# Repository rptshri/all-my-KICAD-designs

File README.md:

View this project on [CADLAB.io](https://cadlab.io/project/2196). 

# all-my-KICAD-designs

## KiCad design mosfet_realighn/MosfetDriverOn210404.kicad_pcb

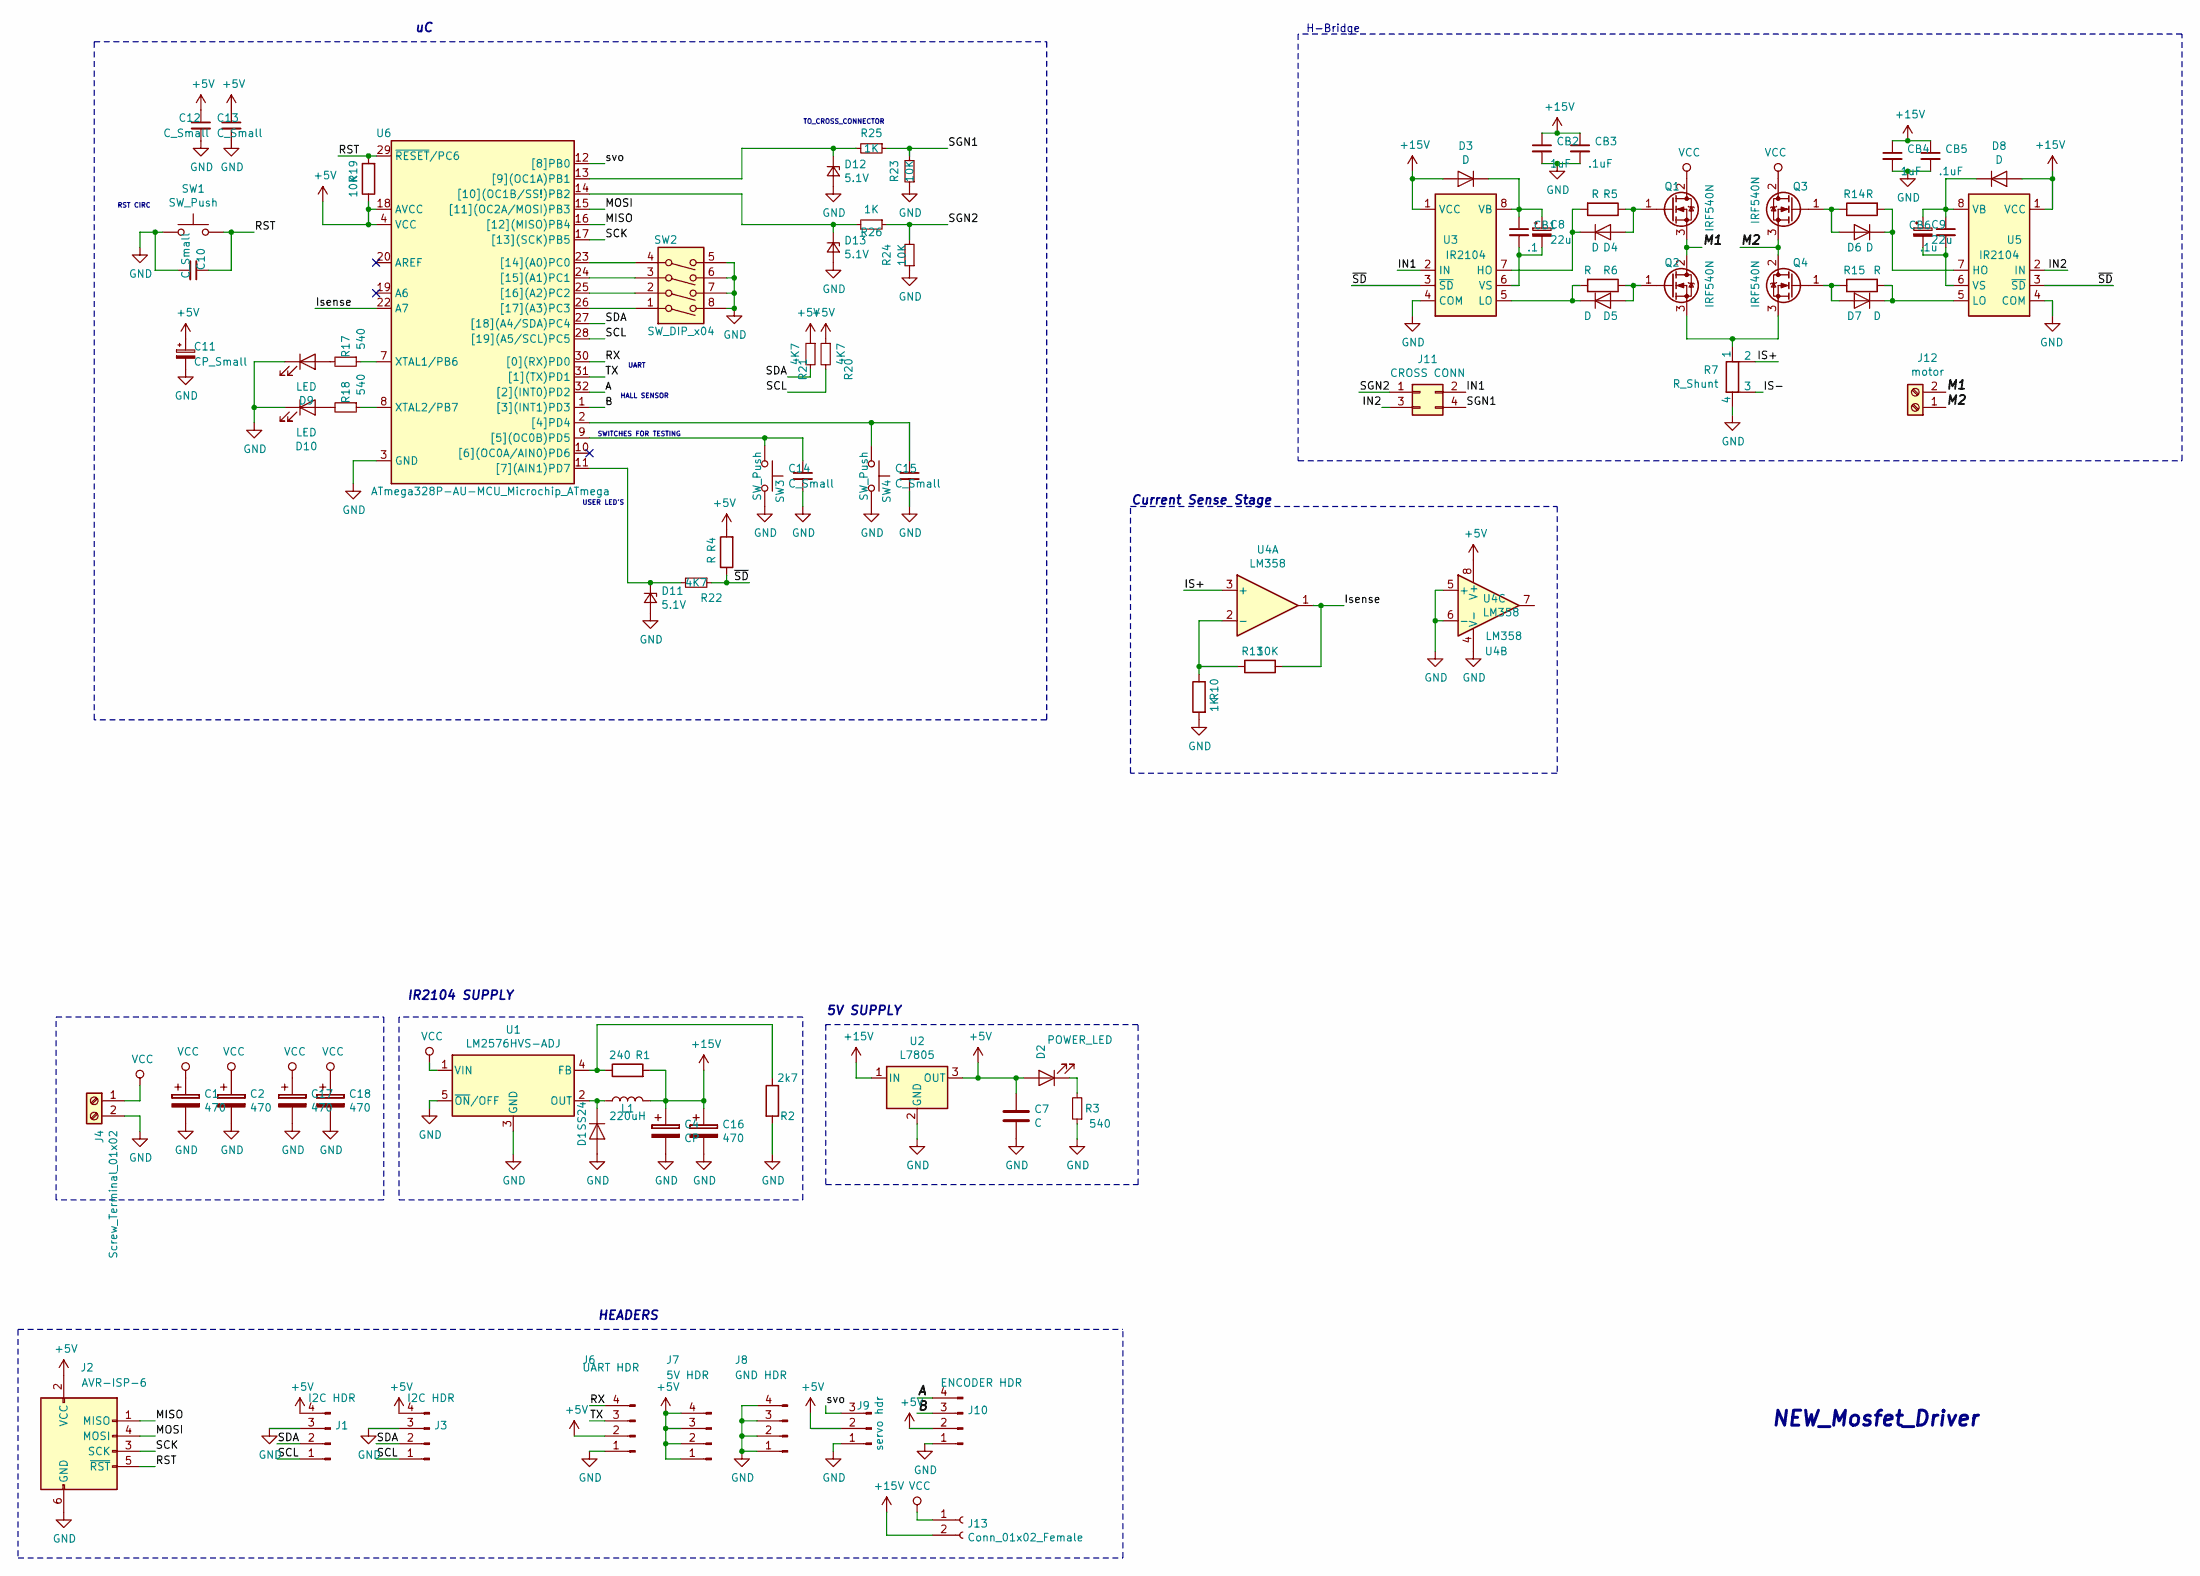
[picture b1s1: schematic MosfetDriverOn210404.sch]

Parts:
C1, C2: 470; CP_Elec_8x6.2
C4: CP; CP_Elec_6.3x5.7
C7: C; C_0603_1608Metric
C8, C9: 22u; CP_Elec_6.3x5.7
C10, C12, C13, C14, C15: C_Small; C_0603_1608Metric
C11: CP_Small; CP_Elec_5x4.4
C16: 470; CP_Elec_6.3x5.7
C17, C18: 470; CP_Elec_10x7.9
CB1: .1; C_0603_1608Metric
CB2, CB4: 1uF; C_0603_1608Metric
CB3, CB5: .1uF; C_0603_1608Metric
CB6: .1u; C_0603_1608Metric
D1: SS24; D_SMA
D2: POWER_LED; LED_0603_1608Metric
D3, D4, D5, D6, D7, D8: D; D_SMA
D9, D10: LED; LED_0603_1608Metric
D11, D12, D13: 5.1V; D_SMA
J1, J3: I2C HDR; JST_PH_B4B-PH-K_1x04_P2.00mm_Vertical
J2: AVR-ISP-6; PinHeader_2x03_P2.54mm_Vertical
J4: Screw_Terminal_01x02; PhoenixContact_MSTBA_2,5_2-G_1x02_P5.00mm_Horizontal
J6: UART HDR; PinHeader_1x04_P2.54mm_Vertical
J7: 5V HDR; PinHeader_1x04_P2.54mm_Vertical
J8: GND HDR; PinHeader_1x04_P2.54mm_Vertical
J9: servo hdr; PinSocket_1x03_P2.54mm_Vertical
J10: ENCODER HDR; PinHeader_1x04_P2.54mm_Vertical
J11: CROSS CONN; PinHeader_2x02_P2.54mm_Vertical
J12: motor; PhoenixContact_MSTBA_2,5_2-G_1x02_P5.00mm_Horizontal
J13: Conn_01x02_Female; PinHeader_1x02_P2.54mm_Vertical
L1: 220uH; L_12x12mm_H6mm
Q1: IRF540N; TO-220-3_Vertical
Q2, Q3, Q4: IRF540N; TO220_HS_SCREW
R1: 240; R_0603_1608Metric
R2: 2k7; R_0603_1608Metric
R3, R17, R18: 540; R_0603_1608Metric
R4, R5, R6, R14, R15: R; R_0603_1608Metric
R7: R_Shunt; Shunt_Resistor-2mohm
R10, R25, R26: 1K; R_0603_1608Metric
R13, R19, R23, R24: 10K; R_0603_1608Metric
R20, R21, R22: 4K7; R_0603_1608Metric
SW1, SW3, SW4: SW_Push; SW_SPST_CK_RS282G05A3
SW2: SW_DIP_x04; SW_DIP_SPSTx04_Slide_9.78x12.34mm_W7.62mm_P2.54mm
U1: LM2576HVS-ADJ; TO-263-5_TabPin3
U2: L7805; SOT-223-3_TabPin2
U3, U5: IR2104; DIP-8_W7.62mm_Socket_LongPads
U4: LM358; SOIC-8_3.9x4.9mm_P1.27mm
U6: ATmega328P-AU-MCU_Microchip_ATmega; TQFP-32_7x7mm_P0.8mm

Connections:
+5V: C7.1, C11.1, C12.1, C13.1, D2.2 (A), J1.4, J2.2 (VCC), J3.4, J6.2, J7.1, J7.2, J7.3, J7.4, J9.2, J10.2, R4.2, R19.1, R20.1, R21.1, U2.3 (OUT), U4.8 (V+), U6.4 (VCC), U6.6 (VCC), U6.18 (AVCC)
+15V: C4.1, C16.1, CB2.1, CB3.1, CB4.1, CB5.1, D3.2 (A), D8.2 (A), J13.2, L1.2, R1.2, U2.1 (IN), U3.1 (VCC), U5.1 (VCC)
/A: J10.4, U6.32 ([2](INT0)PD2)
/B: J10.3, U6.1 ([3](INT1)PD3)
/IN1: J11.2, U3.2 (IN)
/IN2: J11.3, U5.2 (IN)
/IS+: R7.2, U4.3 (+)
/IS-: R7.3
/Isense: R13.2, U4.1, U6.22 (A7)
/M1: J12.2, Q1.3 (S), Q2.2 (D)
/M2: J12.1, Q3.3 (S), Q4.2 (D)
/MISO: J2.1 (MISO), U6.16 ([12](MISO)PB4)
/MOSI: J2.4 (MOSI), U6.15 ([11](OC2A/MOSI)PB3)
/RST: C10.1, J2.5 (~RST), R19.2, SW1.2, U6.29 (~RESET~/PC6)
/RX: J6.4, U6.30 ([0](RX)PD0)
/SCK: J2.3 (SCK), U6.17 ([13](SCK)PB5)
/SCL: J1.1, J3.1, R20.2, U6.28 ([19](A5/SCL)PC5)
/SDA: J1.2, J3.2, R21.2, U6.27 ([18](A4/SDA)PC4)
/SGN1: J11.4, R23.2, R25.1
/SGN2: J11.1, R24.2, R26.1
/TX: J6.3, U6.31 ([1](TX)PD1)
/svo: J9.3, U6.12 ([8]PB0)
/~SD: R4.1, R22.1, U3.3 (~SD), U5.3 (~SD)
GND: C1.2, C2.2, C4.2, C7.2, C10.2, C11.2, C12.2, C13.2, C14.2, C15.2, C16.2, C17.2, C18.2, CB2.2, CB3.2, CB4.2, CB5.2, D1.2 (A), D9.1 (K), D10.1 (K), D11.2 (A), D12.2 (A), D13.2 (A), J1.3, J2.6 (GND), J3.3, J4.2, J6.1, J8.1, J8.2, J8.3, J8.4, J9.1, J10.1, R2.2, R3.1, R7.4, R10.2, R23.1, R24.1, SW1.1, SW2.5, SW2.6, SW2.7, SW2.8, SW3.2, SW4.2, U1.3 (GND), U1.5 (~ON~/OFF), U2.2 (GND), U3.4 (COM), U4.4 (V-), U4.5 (+), U4.6 (-), U5.4 (COM), U6.3 (GND), U6.5 (GND), U6.21 (GND)
unnamed: C8.1, CB1.1, D3.1 (K), U3.8 (VB)
unnamed: C8.2, CB1.2, U3.6 (VS)
unnamed: C9.1, CB6.1, D8.1 (K), U5.8 (VB)
unnamed: C9.2, CB6.2, U5.6 (VS)
unnamed: C14.1, SW3.1, U6.9 ([5](OC0B)PD5)
unnamed: C15.1, SW4.1, U6.2 ([4]PD4)
unnamed: D1.1 (K), L1.1, U1.2 (OUT)
unnamed: D2.1 (K), R3.2
unnamed: D4.1 (K), R5.2, U3.7 (HO)
unnamed: D4.2 (A), Q1.1 (G), R5.1
unnamed: D5.1 (K), R6.2, U3.5 (LO)
unnamed: D5.2 (A), Q2.1 (G), R6.1
unnamed: D6.1 (K), R14.2, U5.7 (HO)
unnamed: D6.2 (A), Q3.1 (G), R14.1
unnamed: D7.1 (K), R15.2, U5.5 (LO)
unnamed: D7.2 (A), Q4.1 (G), R15.1
unnamed: D9.2 (A), R17.2
unnamed: D10.2 (A), R18.2
unnamed: D11.1 (K), R22.2, U6.11 ([7](AIN1)PD7)
unnamed: D12.1 (K), R25.2, U6.13 ([9](OC1A)PB1)
unnamed: D13.1 (K), R26.2, U6.14 ([10](OC1B/SS!)PB2)
unnamed: Q2.3 (S), Q4.3 (S), R7.1
unnamed: R1.1, R2.1, U1.4 (FB)
unnamed: R10.1, R13.1, U4.2 (-)
unnamed: R17.1, U6.7 (XTAL1/PB6)
unnamed: R18.1, U6.8 (XTAL2/PB7)
unnamed: SW2.1, U6.26 ([17](A3)PC3)
unnamed: SW2.2, U6.25 ([16](A2)PC2)
unnamed: SW2.3, U6.24 ([15](A1)PC1)
unnamed: SW2.4, U6.23 ([14](A0)PC0)
VCC: C1.1, C2.1, C17.1, C18.1, J4.1, J13.1, Q1.2 (D), Q3.2 (D), U1.1 (VIN)

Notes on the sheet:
NEW_Mosfet_Driver
HEADERS
5V SUPPLY
IR2104 SUPPLY
HALL SENSOR
UART
SWITCHES FOR TESTING
USER LED'S
TO_CROSS_CONNECTOR
RST CIRC
H-Bridge
Current Sense Stage

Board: 2 copper layers, 82 parts (0 on the bottom side), 54 nets, no tracks yet.

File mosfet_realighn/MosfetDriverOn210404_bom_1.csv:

Component,Description,Part,References,Value,Footprint,Quantity Per PCB,Datasheet
1,Unpolarized capacitor,C_Small,C10 C12 C13 C14 C15 CB3 CB5 CB6,0.1u,C_0805_2012Metric,8,~
2,Polarised capacitor,CP,C4,100u,CP_Elec_6.3x5.7,1,~
3,Polarised capacitor,CP_Small,C11,10u,CP_Elec_5x4.4,1,~
4,Unpolarized capacitor,C,C7 CB2 CB4,1u,C_0805_2012Metric,3,~
5,Polarised capacitor,CP_Small,C8 C9,22u,CP_Elec_5x5.3,2,~
6,Polarised capacitor,CP,C1 C2,470u,CP_Elec_8x6.2,2,~
7,Polarised capacitor,CP,C16 C17 C18,470u,CP_Elec_10x7.9,3,~
8,Unpolarized capacitor,C_Small,CB1,.1,C_0805_2012Metric,1,~
9,"Zener Diode, small symbol",D_Zener_Small,D11 D12 D13,5.1V,D_A-405_P7.62mm_Horizontal,3,~
10,Diode,D,D3 D4 D5 D6 D7 D8,D,D_SMA,6,~
11,LED generic,LED,D9 D10,LED,LED_0805_2012Metric,2,~
12,LED generic,LED,D2,POWER_LED,LED_0805_2012Metric,1,~
13,Diode,D,D1,SS24,D_SMC,1,~
14,"Generic connector, single row, 01x04, script generated (kicad-library-utils/schlib/autogen/connector/)",Conn_01x04_Male,J7,5V HDR,PinHeader_1x04_P2.54mm_Vertical,1,~
15,Atmel 6-pin ISP connector,AVR-ISP-6,J2,AVR-ISP-6,PinHeader_2x03_P2.54mm_Vertical,1, ~
16,"Generic connector, double row, 02x02, odd/even pin numbering scheme (row 1 odd numbers, row 2 even numbers), script generated (kicad-library-utils/schlib/autogen/connector/)",Conn_02x02_Odd_Even,J11,CROSS CONN,PinHeader_2x02_P2.54mm_Vertical,1,~
17,"Generic connector, single row, 01x02, script generated (kicad-library-utils/schlib/autogen/connector/)",Conn_01x02_Female,J13,Conn_01x02_Female,PinHeader_1x02_P2.54mm_Vertical,1,~
18,"Generic connector, single row, 01x04, script generated (kicad-library-utils/schlib/autogen/connector/)",Conn_01x04_Male,J10,ENCODER HDR,PinHeader_1x04_P2.54mm_Vertical,1,~
19,"Generic connector, single row, 01x04, script generated (kicad-library-utils/schlib/autogen/connector/)",Conn_01x04_Male,J8,GND HDR,PinHeader_1x04_P2.54mm_Vertical,1,~
20,"Generic connector, single row, 01x04, script generated (kicad-library-utils/schlib/autogen/connector/)",Conn_01x04_Male,J1 J3 J5,I2C HDR,PinHeader_1x04_P2.54mm_Vertical,3,~
21,"Generic screw terminal, single row, 01x02, script generated (kicad-library-utils/schlib/autogen/connector/)",Screw_Terminal_01x02,J4,Screw_Terminal_01x02,TerminalBlock_Altech_AK300-2_P5.00mm,1,~
22,"Generic connector, single row, 01x04, script generated (kicad-library-utils/schlib/autogen/connector/)",Conn_01x04_Male,J6,UART HDR,PinHeader_1x04_P2.54mm_Vertical,1,~
23,"Generic screw terminal, single row, 01x02, script generated (kicad-library-utils/schlib/autogen/connector/)",Screw_Terminal_01x02,J12,motor,TerminalBlock_Altech_AK300-2_P5.00mm,1,~
24,"Generic connector, single row, 01x03, script generated (kicad-library-utils/schlib/autogen/connector/)",Conn_01x03_Male,J9,servo hdr,PinSocket_1x03_P2.54mm_Vertical,1,~
25,Inductor,L,L1,220uH,L_12x12mm_H6mm,1,~
26,"33A Id, 100V Vds, HEXFET N-Channel MOSFET, TO-220",IRF540N,Q1 Q2 Q3 Q4,IRF540N,TO220_HS_SCREW,4,http://www.irf.com/product-info/datasheets/data/irf540n.pdf
27,Resistor,R,R7 R8 R9 R11 R12,0E05,R_2512_6332Metric,5,~
28,Resistor,R,R5 R6 R14 R15,10,R_0805_2012Metric,4,~
29,Resistor,R,R13 R19 R23 R24,10K,R_0805_2012Metric,4,~
30,Resistor,R,R10 R25 R26,1K,R_0805_2012Metric,3,~
31,Resistor,R,R1,240,R_0805_2012Metric,1,~
32,Resistor,R,R2,2k7,R_0805_2012Metric,1,~
33,Resistor,R,R4 R20 R21 R22,4K7,R_0805_2012Metric,4,~
34,"Resistor, small symbol",R_Small,R3 R17 R18,540,R_0805_2012Metric,3,~
35,"4x DIP Switch, Single Pole Single Throw (SPST) switch, small symbol",SW_DIP_x04,SW2,SW_DIP_x04,SW_DIP_SPSTx04_Slide_9.78x12.34mm_W7.62mm_P2.54mm,1,
36,"Push button switch, generic, two pins",SW_Push,SW1 SW3 SW4,SW_Push,SW_PUSH_6mm,3,
37,,ATmega328P-AU-MCU_Microchip_ATmega,U6,ATmega328P-AU-MCU_Microchip_ATmega,TQFP-32_7x7mm_P0.8mm,1,
38,"High and Low Side Gate Driver,  Output Current 130/270mA, PDIP-8/SOIC-8",IR2104,U3 U5,IR2104,DIP-8_W7.62mm_Socket_LongPads,2,http://www.irf.com/product-info/datasheets/data/ir2104.pdf
39,"Positive 1.5A 35V Linear Regulator, Fixed Output 5V, TO-220/TO-263/TO-252",L7805,U2,L7805,SOT-223-3_TabPin2,1,http://www.st.com/content/ccc/resource/technical/document/da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
40,"Adjustable Output Voltage, 3A SIMPLE SWITCHER® Step-Down Voltage Regulator, High Voltage Input, TO-263",LM2576HVS-ADJ,U1,LM2576HVS-ADJ,TO-263-5_TabPin3,1,http://www.ti.com/lit/ds/symlink/lm2576.pdf
41,"Low-Power, Dual Operational Amplifiers, DIP-8/SOIC-8/TO-99-8",LM358,U4,LM358,SOIC-8_3.9x4.9mm_P1.27mm,1,http://www.ti.com/lit/ds/symlink/lm2904-n.pdf





Component Groups:,41
Component Count:,87
Fitted Components:,87
Number of PCBs:,1
Total components:,87
Schematic Version:,1
Schematic Date:,2018-10-21
BoM Date:,10/27/2018 10:03:15 AM
Schematic Source:,C:\Users\malha\OneDrive\Documents\GitHub\Mosfet_Driver-NEW-\MosfetDriverOn2104\MosfetDriverOn210404.sch
KiCad Version:,Eeschema (5.0.0)

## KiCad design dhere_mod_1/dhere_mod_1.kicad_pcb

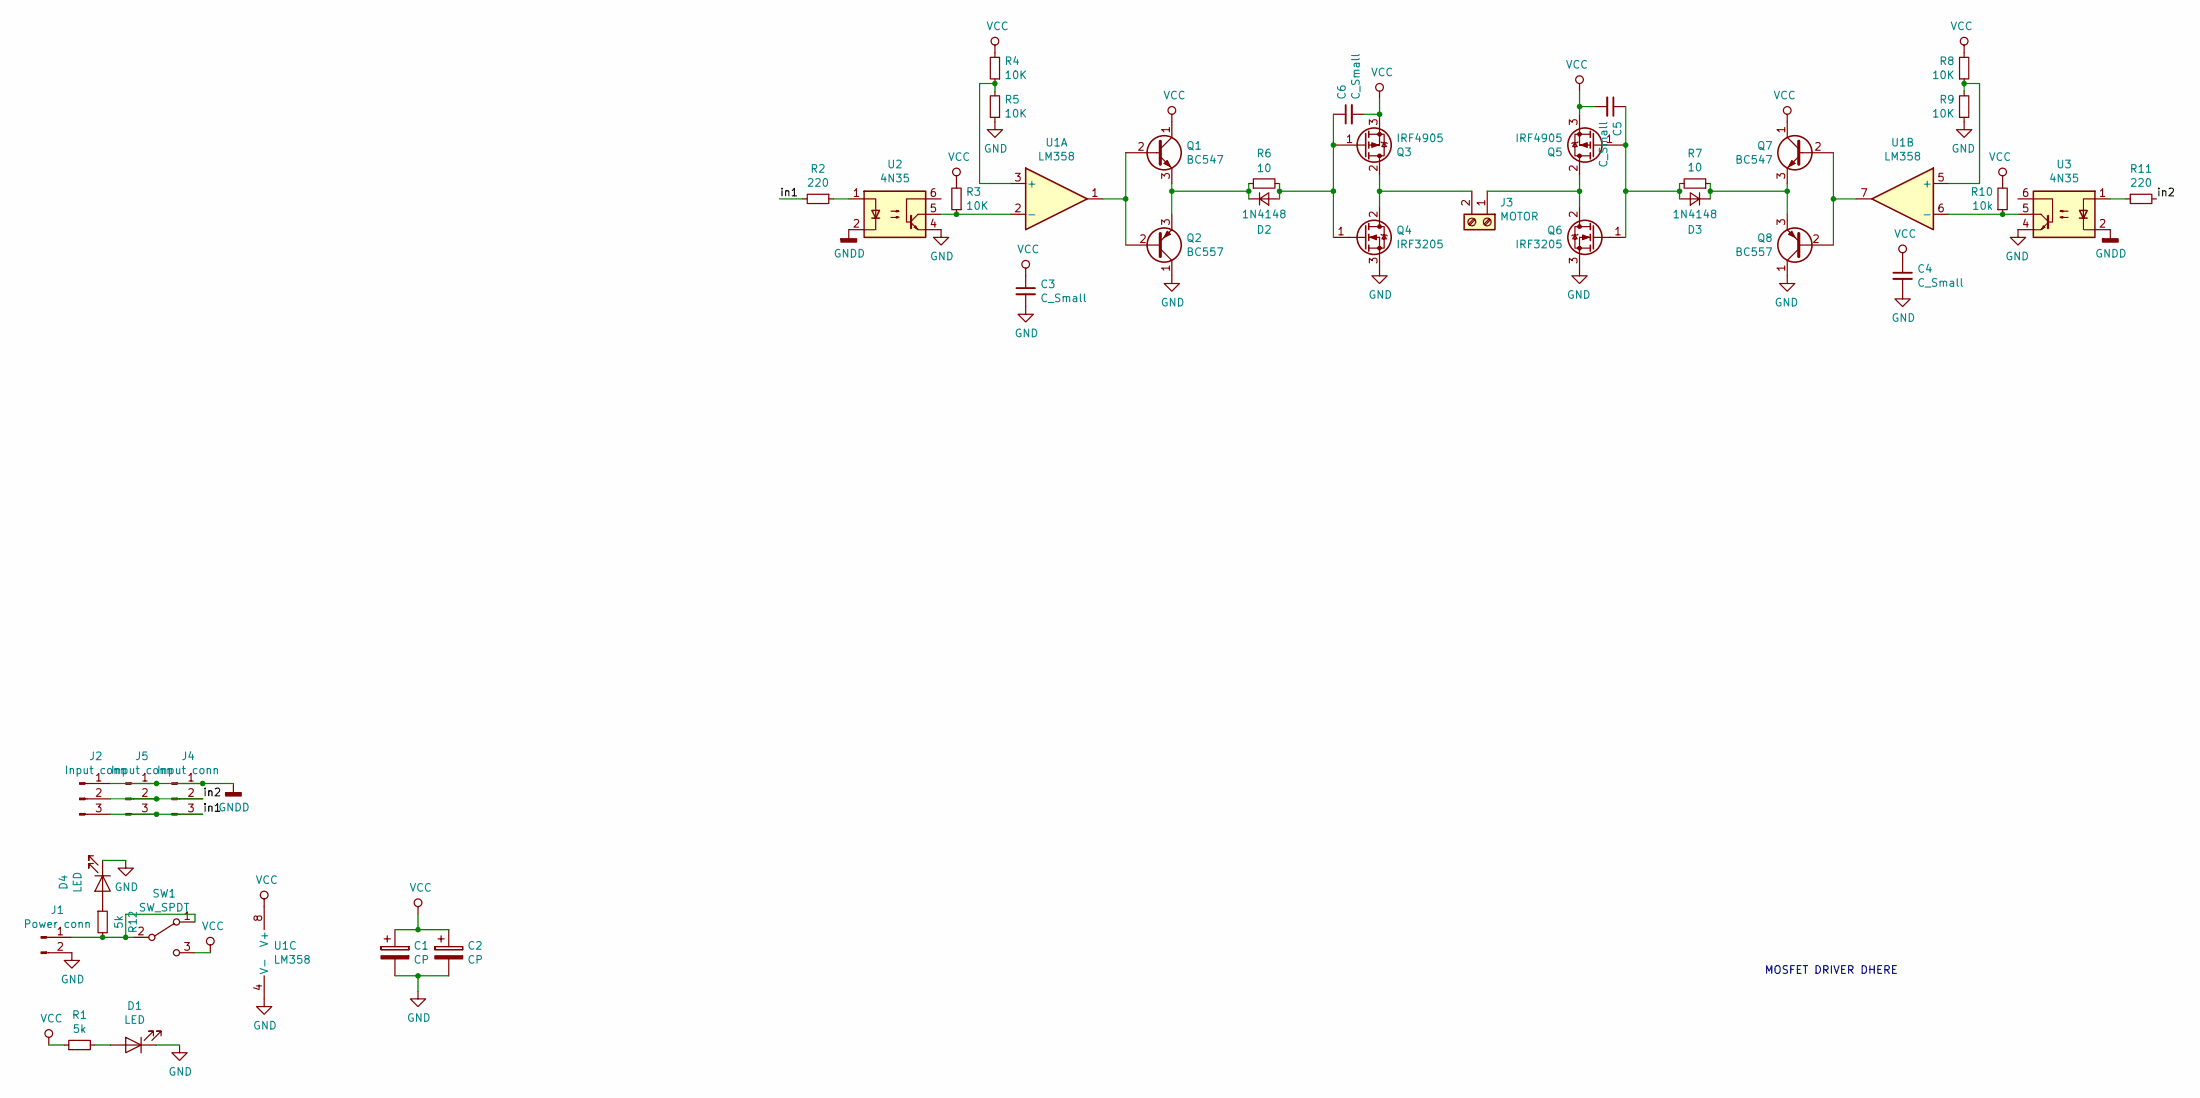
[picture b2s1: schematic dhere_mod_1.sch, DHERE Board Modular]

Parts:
C1, C2: CP; CP_Radial_D10.0mm_P2.50mm_P5.00mm
C3, C4, C5, C6: C_Small; C_0805_2012Metric
D1, D4: LED; LED_D5.0mm_FlatTop
D2, D3: 1N4148; D_A-405_P7.62mm_Horizontal
J1: Power conn; TerminalBlock_Altech_AK300-2_P5.00mm
J2: Input conn; JST_EH_S03B-EH_1x03_P2.50mm_Horizontal
J3: MOTOR; TerminalBlock_Altech_AK300-2_P5.00mm
J4, J5: Input conn; PinHeader_1x03_P2.54mm_Vertical
Q1, Q7: BC547; TO-92_Wide
Q2, Q8: BC557; TO-92_Wide
Q3, Q5: IRF4905; TO-220-3_Vertical
Q4, Q6: IRF3205; TO-220-3_Vertical
R1, R12: 5k; R_0805_2012Metric_Pad1.15x1.40mm_HandSolder
R2, R11: 220; R_Axial_DIN0207_L6.3mm_D2.5mm_P7.62mm_Horizontal
R3, R4, R5, R8, R9: 10K; R_Axial_DIN0207_L6.3mm_D2.5mm_P7.62mm_Horizontal
R6, R7: 10; R_Axial_DIN0207_L6.3mm_D2.5mm_P7.62mm_Horizontal
R10: 10k; R_Axial_DIN0207_L6.3mm_D2.5mm_P7.62mm_Horizontal
SW1: SW_SPDT; SW_CuK_OS102011MA1QN1_SPDT_Angled
U1: LM358; DIP-8_W7.62mm_Socket_LongPads
U2, U3: 4N35; DIP-6_W7.62mm

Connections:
/in1: J2.3, J4.3, J5.3, R2.2
/in2: J2.2, J4.2, J5.2, R11.2
GND: C1.2, C2.2, C3.2, C4.2, D1.1 (K), D4.1 (K), J1.2, Q2.1 (C), Q4.3 (S), Q6.3 (S), Q8.1 (C), R5.1, R9.1, U1.4 (V-), U2.4, U3.4
GNDD: J2.1, J4.1, J5.1, U2.2, U3.2
unnamed: C5.1, D3.2 (A), Q5.1 (G), Q6.1 (G), R7.2
unnamed: C6.1, D2.2 (A), Q3.1 (G), Q4.1 (G), R6.2
unnamed: D1.2 (A), R1.2
unnamed: D2.1 (K), Q1.3 (E), Q2.3 (E), R6.1
unnamed: D3.1 (K), Q7.3 (E), Q8.3 (E), R7.1
unnamed: D4.2 (A), R12.1
unnamed: J1.1, R12.2, SW1.1 (A), SW1.2 (B)
unnamed: J3.1, Q5.2 (D), Q6.2 (D)
unnamed: J3.2, Q3.2 (D), Q4.2 (D)
unnamed: Q1.2 (B), Q2.2 (B), U1.1
unnamed: Q7.2 (B), Q8.2 (B), U1.7
unnamed: R2.1, U2.1
unnamed: R3.1, U1.2 (-), U2.5
unnamed: R4.1, R5.2, U1.3 (+)
unnamed: R8.1, R9.2, U1.5 (+)
unnamed: R10.1, U1.6 (-), U3.5
unnamed: R11.1, U3.1
VCC: C1.1, C2.1, C3.1, C4.1, C5.2, C6.2, Q1.1 (C), Q3.3 (S), Q5.3 (S), Q7.1 (C), R1.1, R3.2, R4.2, R8.2, R10.2, SW1.3 (C), U1.8 (V+)

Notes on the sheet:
MOSFET DRIVER DHERE

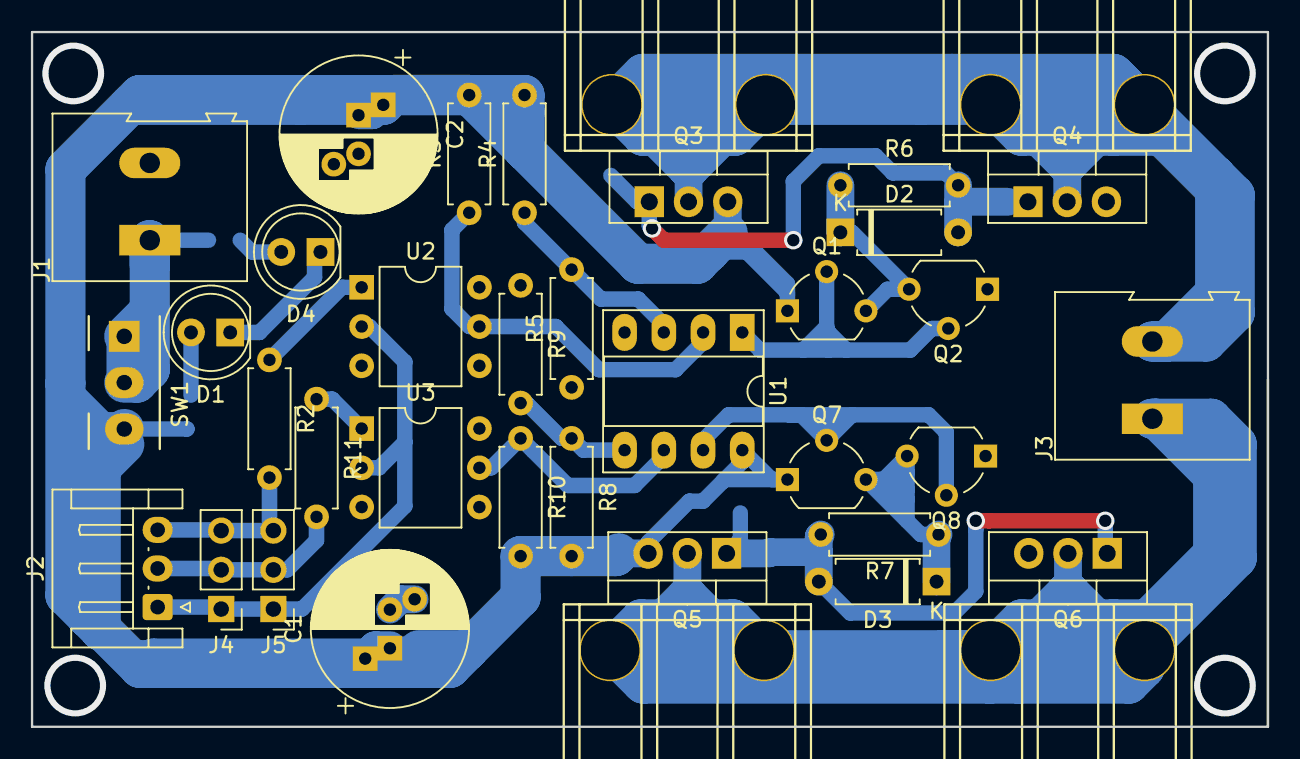
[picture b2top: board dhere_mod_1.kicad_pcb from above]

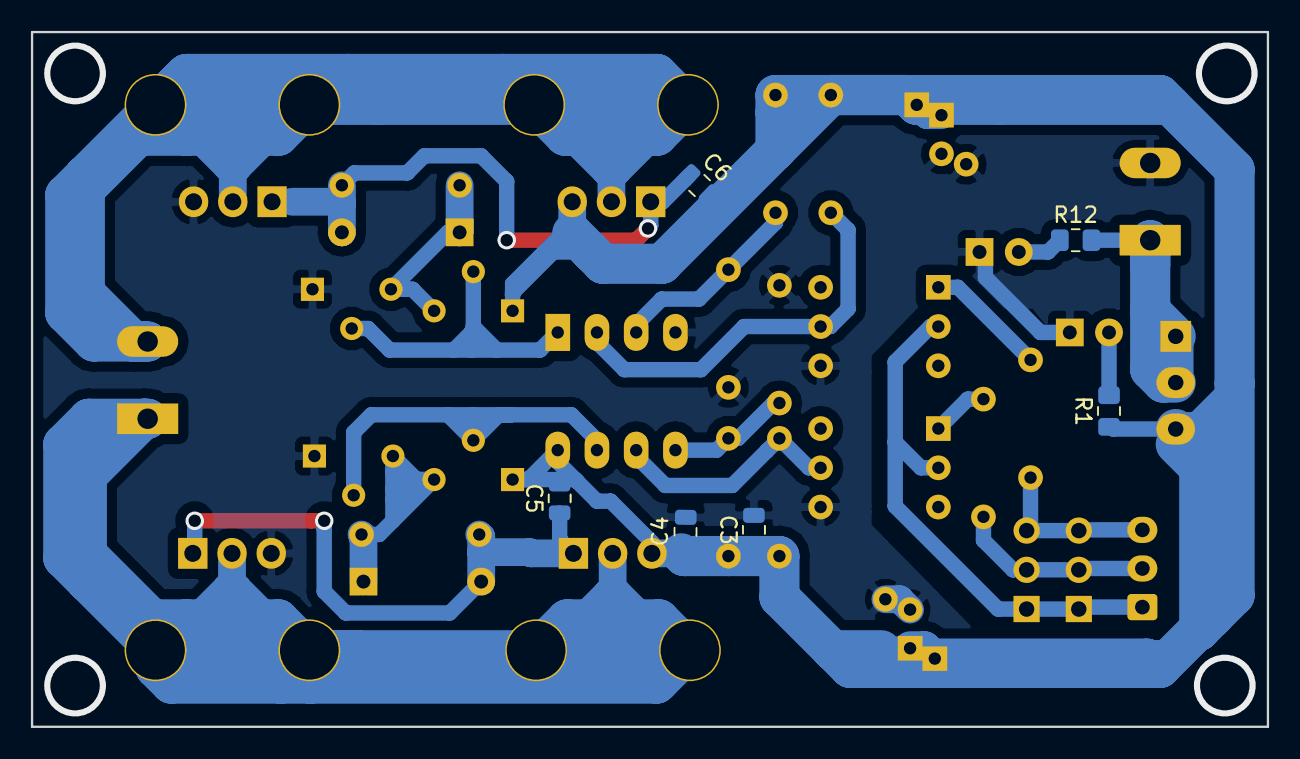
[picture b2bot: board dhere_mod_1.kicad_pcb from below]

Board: 2 copper layers, 80.0 x 45.0 mm, 39 parts (6 on the bottom side), 22 nets.

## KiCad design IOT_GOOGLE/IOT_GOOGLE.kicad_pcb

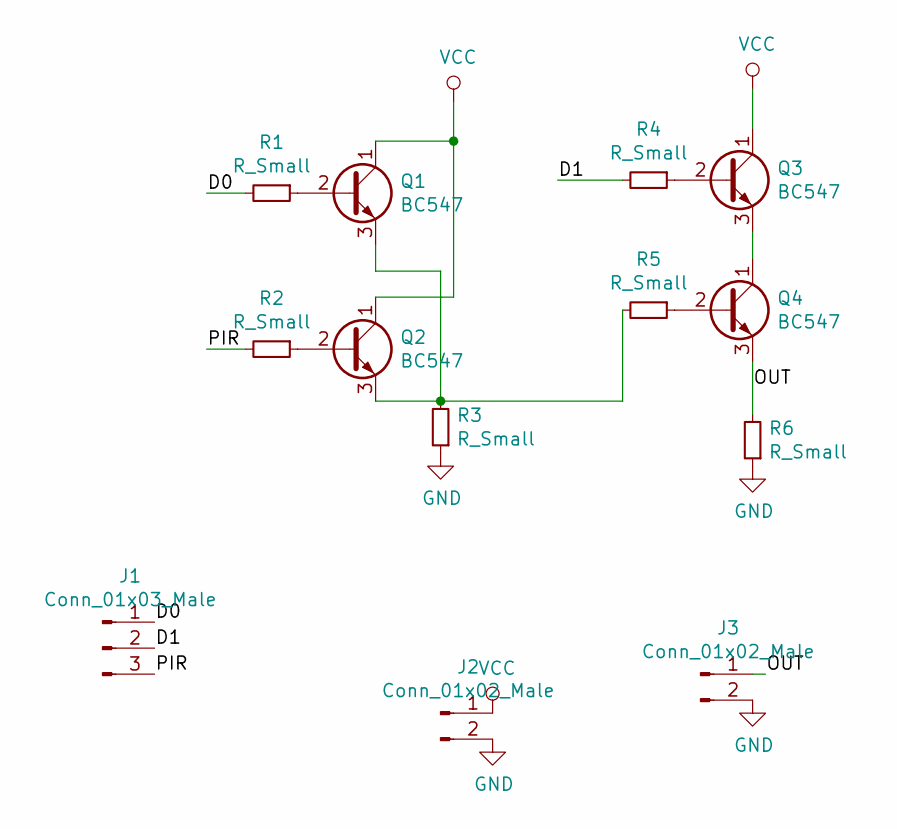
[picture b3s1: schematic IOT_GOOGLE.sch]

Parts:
J1: Conn_01x03_Male; PinHeader_1x03_P2.54mm_Vertical
J2, J3: Conn_01x02_Male; PinHeader_1x02_P2.54mm_Vertical
Q1, Q2, Q3, Q4: BC547; TO-92_Wide
R1, R2, R3, R4, R5, R6: R_Small; R_Axial_DIN0207_L6.3mm_D2.5mm_P7.62mm_Horizontal

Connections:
/D0: J1.1, R1.2
/D1: J1.2, R4.2
/OUT: J3.1, Q4.3 (E), R6.2
/PIR: J1.3, R2.2
GND: J2.2, J3.2, R3.1, R6.1
unnamed: Q1.2 (B), R1.1
unnamed: Q1.3 (E), Q2.3 (E), R3.2, R5.2
unnamed: Q2.2 (B), R2.1
unnamed: Q3.2 (B), R4.1
unnamed: Q3.3 (E), Q4.1 (C)
unnamed: Q4.2 (B), R5.1
VCC: J2.1, Q1.1 (C), Q2.1 (C), Q3.1 (C)

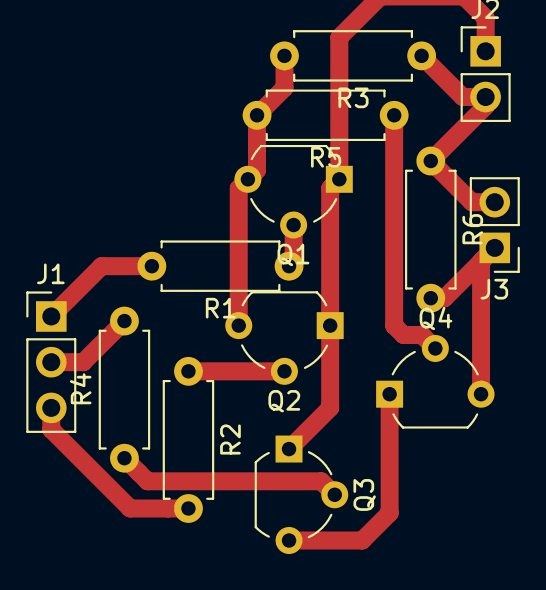
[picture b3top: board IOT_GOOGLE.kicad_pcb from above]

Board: 2 copper layers, 13 parts (0 on the bottom side), 12 nets.

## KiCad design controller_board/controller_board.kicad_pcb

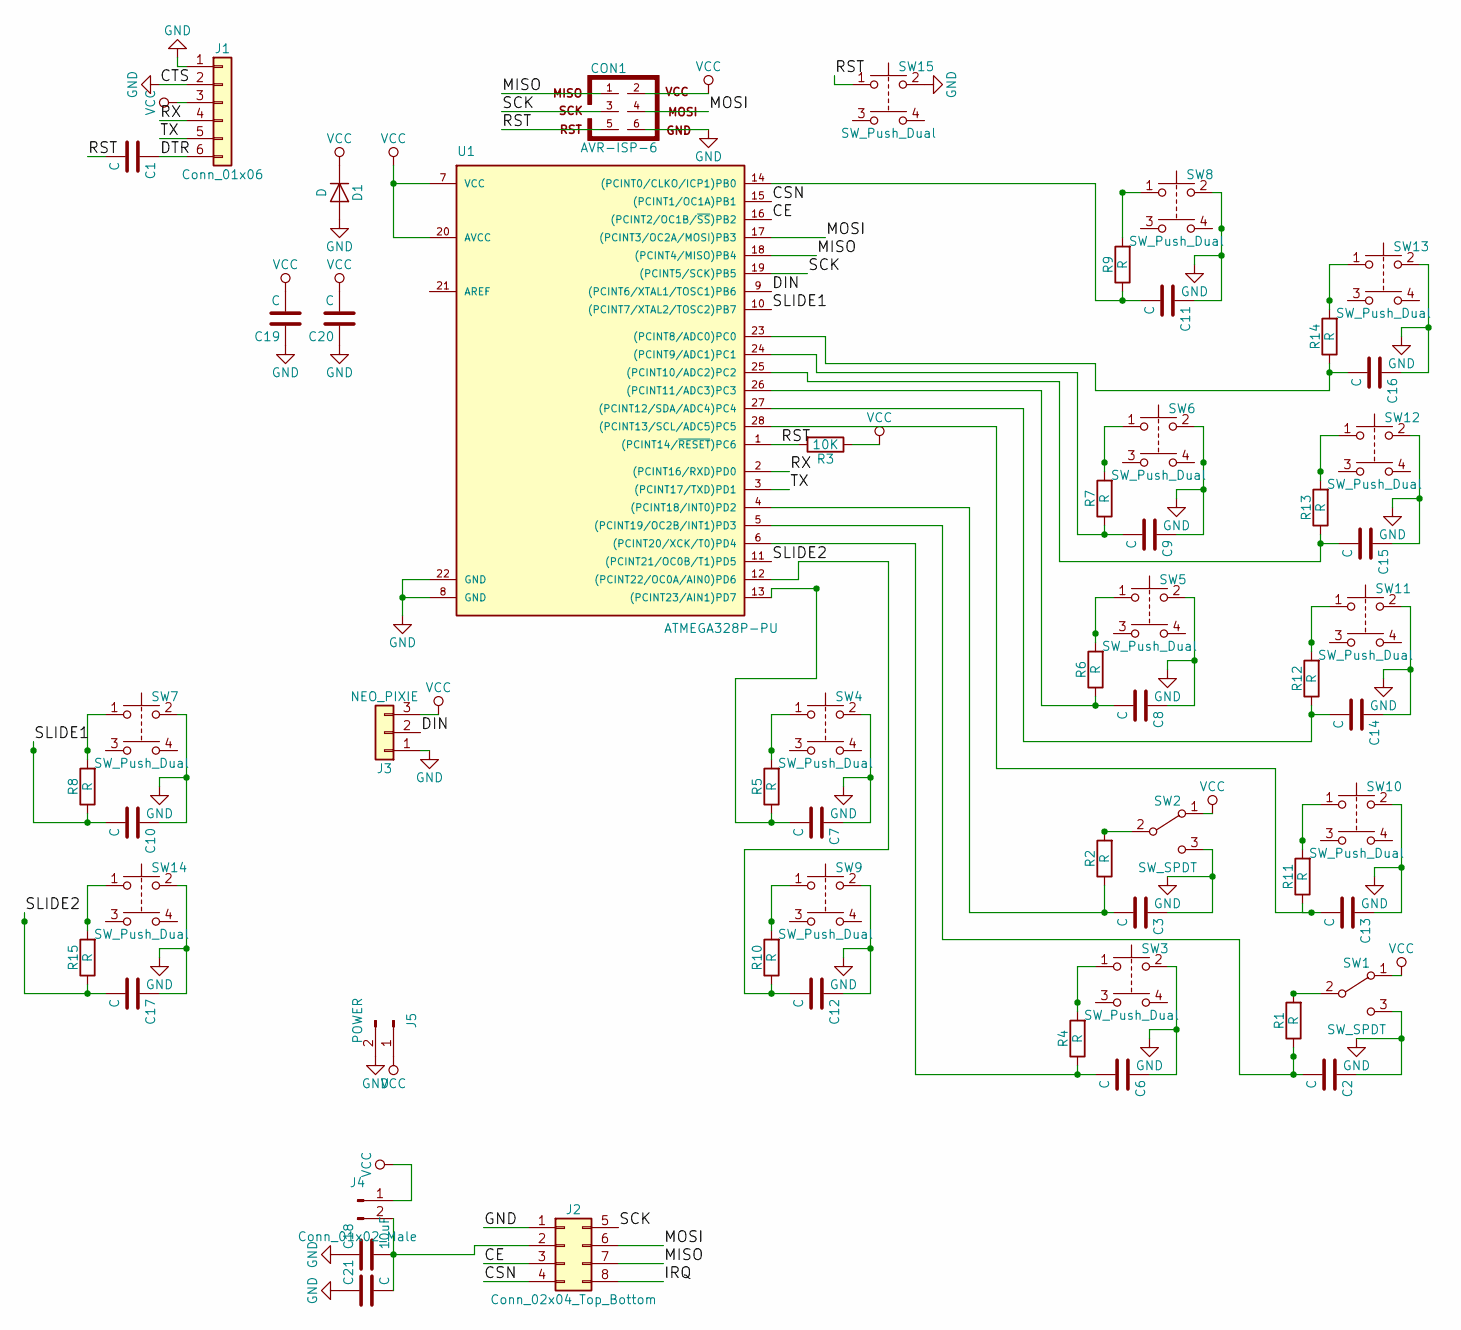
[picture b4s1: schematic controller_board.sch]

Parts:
C1, C2, C3, C6, C7, C8, C9, C10, C11, C12, C13, C14, C15, C16, C17, C19, C20, C21: C; C_Disc_D3.4mm_W2.1mm_P2.50mm
C18: 10uF; C_Disc_D3.4mm_W2.1mm_P2.50mm
CON1: AVR-ISP-6; Pin_Header_Straight_2x03_Pitch2.54mm
D1: D; R_Axial_DIN0207_L6.3mm_D2.5mm_P7.62mm_Horizontal
J1: Conn_01x06; Pin_Header_Straight_1x06_Pitch2.54mm
J2: Conn_02x04_Top_Bottom; Pin_Header_Straight_2x04_Pitch2.54mm
J3: NEO_PIXIE; Pin_Header_Straight_1x03_Pitch2.54mm
J4: Conn_01x02_Male; Pin_Header_Straight_1x02_Pitch2.54mm
J5: POWER; Pin_Header_Straight_1x02_Pitch2.54mm
R1, R2, R4, R5, R6, R7, R8, R9, R10, R11, R12, R13, R14, R15: R; R_Axial_DIN0207_L6.3mm_D2.5mm_P7.62mm_Horizontal
R3: 10K; R_Axial_DIN0207_L6.3mm_D2.5mm_P7.62mm_Horizontal
SW1, SW2: SW_SPDT; SW_CuK_OS102011MA1QN1_SPDT_Angled
SW3, SW4, SW5, SW6, SW7, SW8, SW9, SW10, SW11, SW12, SW13, SW14, SW15: SW_Push_Dual; SW_PUSH_6mm
U1: ATMEGA328P-PU; DIP-28_W7.62mm_LongPads

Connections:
/CE: J2.3, U1.16 ((PCINT2/OC1B/~SS~)PB2)
/CSN: J2.4, U1.15 ((PCINT1/OC1A)PB1)
/DIN: J3.2, U1.9 ((PCINT6/XTAL1/TOSC1)PB6)
/DTR: C1.1, J1.6
/IRQ: J2.8
/MISO: CON1.1, J2.7, U1.18 ((PCINT4/MISO)PB4)
/MOSI: CON1.4, J2.6, U1.17 ((PCINT3/OC2A/MOSI)PB3)
/RST: C1.2, CON1.5, R3.2, SW15.1, U1.1 ((PCINT14/~RESET~)PC6)
/RX: J1.4, U1.2 ((PCINT16/RXD)PD0)
/SCK: CON1.3, J2.5, U1.19 ((PCINT5/SCK)PB5)
/SLIDE1: C10.2, R8.1, U1.10 ((PCINT7/XTAL2/TOSC2)PB7)
/SLIDE2: C17.2, R15.1, U1.11 ((PCINT21/OC0B/T1)PD5)
/TX: J1.5, U1.3 ((PCINT17/TXD)PD1)
GND: C2.1, C3.1, C6.1, C7.1, C8.1, C9.1, C10.1, C11.1, C12.1, C13.1, C14.1, C15.1, C16.1, C17.1, C18.1, C19.1, C20.1, C21.1, CON1.6, D1.2 (A), J1.1, J1.2, J2.1, J3.1, J5.2, SW1.3 (C), SW2.3 (C), SW3.2, SW4.2, SW5.2, SW6.2, SW7.2, SW8.2, SW9.2, SW10.2, SW11.2, SW12.2, SW13.2, SW14.2, SW15.2, U1.8 (GND), U1.22 (GND)
unnamed: C2.2, R1.1, U1.5 ((PCINT19/OC2B/INT1)PD3)
unnamed: C3.2, R2.1, U1.4 ((PCINT18/INT0)PD2)
unnamed: C6.2, R4.1, U1.6 ((PCINT20/XCK/T0)PD4)
unnamed: C7.2, R5.1, U1.13 ((PCINT23/AIN1)PD7)
unnamed: C8.2, R6.1, U1.26 ((PCINT11/ADC3)PC3)
unnamed: C9.2, R7.1, U1.24 ((PCINT9/ADC1)PC1)
unnamed: C11.2, R9.1, U1.14 ((PCINT0/CLKO/ICP1)PB0)
unnamed: C12.2, R10.1, U1.12 ((PCINT22/OC0A/AIN0)PD6)
unnamed: C13.2, R11.1, U1.28 ((PCINT13/SCL/ADC5)PC5)
unnamed: C14.2, R12.1, U1.27 ((PCINT12/SDA/ADC4)PC4)
unnamed: C15.2, R13.1, U1.25 ((PCINT10/ADC2)PC2)
unnamed: C16.2, R14.1, U1.23 ((PCINT8/ADC0)PC0)
unnamed: C18.2, C21.2, J2.2, J4.2
unnamed: R1.2, SW1.2 (B)
unnamed: R2.2, SW2.2 (B)
unnamed: R4.2, SW3.1
unnamed: R5.2, SW4.1
unnamed: R6.2, SW5.1
unnamed: R7.2, SW6.1
unnamed: R8.2, SW7.1
unnamed: R9.2, SW8.1
unnamed: R10.2, SW9.1
unnamed: R11.2, SW10.1
unnamed: R12.2, SW11.1
unnamed: R13.2, SW12.1
unnamed: R14.2, SW13.1
unnamed: R15.2, SW14.1
VCC: C19.2, C20.2, CON1.2, D1.1 (K), J1.3, J3.3, J4.1, J5.1, R3.1, SW1.1 (A), SW2.1 (A), U1.7 (VCC), U1.20 (AVCC)

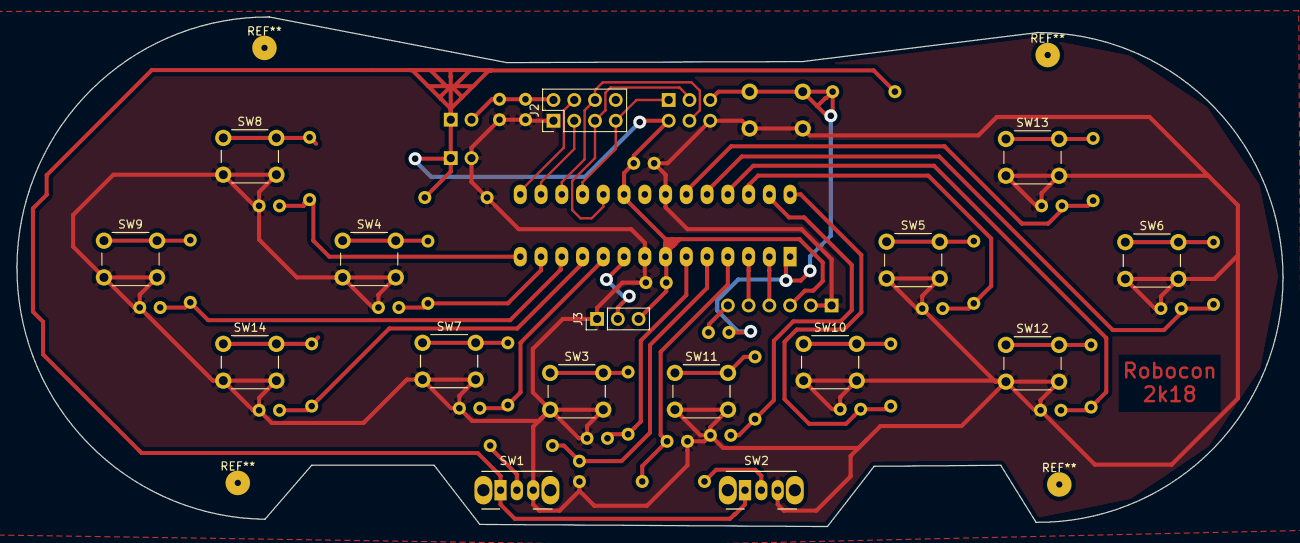
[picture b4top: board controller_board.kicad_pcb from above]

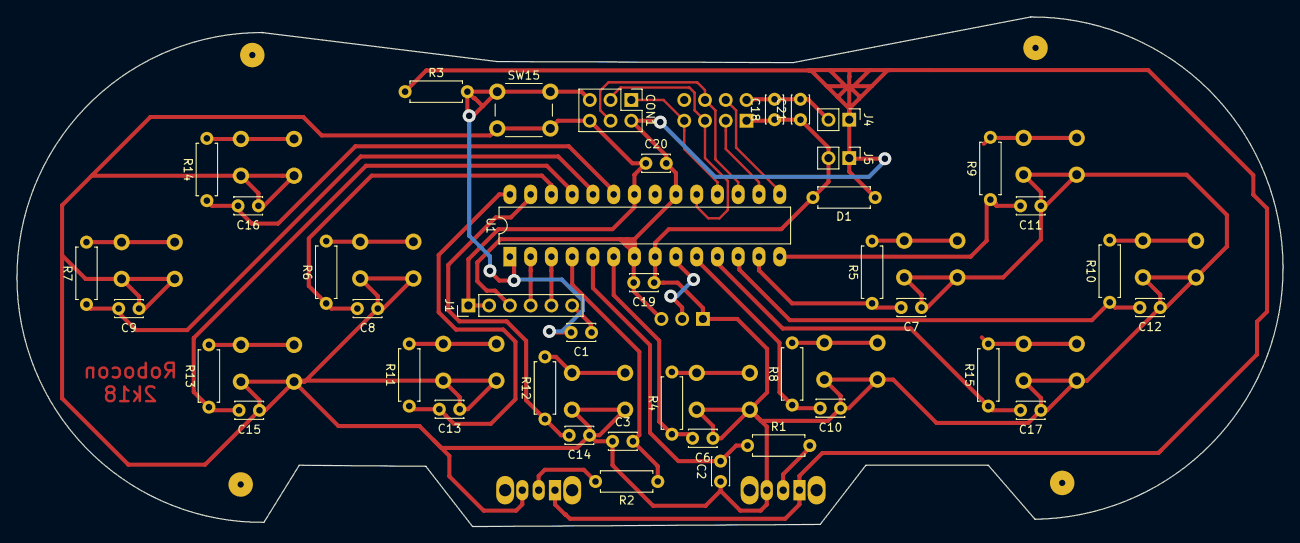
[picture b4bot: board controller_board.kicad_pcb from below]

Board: 2 copper layers, 154.9 x 62.4 mm, 57 parts (41 on the bottom side), 41 nets.
